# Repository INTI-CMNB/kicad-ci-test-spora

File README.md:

# KiCad CI/CD test using Spora

This project is a demo of [CI/CD](https://en.wikipedia.org/wiki/Continuous_integration) for [KiCad](https://www.kicad.org/)

## Objetive

Automate the following tasks:
* ERC and DRC checks
* PDF versions of the schematic and PCB for documentation
* Generation of fabrication files (BoMs, gerbers, drill, position, 3D model, etc.)

## Tools used

To automate the process here we use:
* [KiBot](https://github.com/INTI-CMNB/KiBot) to generate gerbers, drill, position files and BoMs (HTML, XLSX and CSV)
* [kicad-automation-scripts](https://github.com/INTI-CMNB/kicad-automation-scripts) to run DRC/ERC, print schematics and PCB
* [InteractiveHtmlBom](https://github.com/INTI-CMNB/InteractiveHtmlBom) to generate interactive HTML BoMs
* [PcbDraw](https://github.com/INTI-CMNB/PcbDraw) to generate the PCB previews using different colors
* Docker to integrate KiCad and all the tools in a single package suitable for CI/CD pipelines
* GitHub CI/CD pipeline mechanism

The docker image can be found [here](https://github.com/INTI-CMNB/kicad_auto)

## Test project

As a testbed we are using the [Spora](https://github.com/INTI-CMNB/spora) project. It contains three separated boards:
* **pcb_io** is the I/O module. 2 layers
* **pcb_main** is the main module. 6 layers.
* **pcb_prog** is the programmer interface. 2 layers.

## Here is what we test

The pipeline we test here runs 3 workflows, one for each PCB. Each workflow runs 4 jobs:

- ERC: Runs the Electrical Rules Check (schematic test).
- Schematic fabrication files: Generates all the outputs related to the schematic. Runs only if the ERC was successful.
- DRC: Runs the Design Rules Check (PCB test). Runs only if the ERC was successful.
- PCB fabrication files: Generates all the outputs related to the PCB. Runs only if the DRC was successful.

When a commit affects any of the schematics, PCBs or the associated Makefiles the workflow is started.

The configuration for the workflows can be found here: [.github/workflows/](https://github.com/INTI-CMNB/kicad-ci-test-spora/tree/master/.github/workflows)

To get the generated outputs you must enter in one of the workflows, [here is an example](https://github.com/INTI-CMNB/kicad-ci-test-spora/actions/runs/562325892).
Use the `Actions` option at the top of the page.

## Here is what we get

The summary of each workflow contains the generated files in a compressed ZIP. In the GitHub dialect these are the *artifacts*.
Here are links to the run #5 (2021-02-12):

- Main board:
  - [ERC report](https://github.com/INTI-CMNB/kicad-ci-test-spora/suites/2030327470/artifacts/40807405)
  - [DRC report](https://github.com/INTI-CMNB/kicad-ci-test-spora/suites/2030327470/artifacts/40807404)
  - [Schematic related stuff](https://github.com/INTI-CMNB/kicad-ci-test-spora/suites/2030327470/artifacts/40807407)
  - [PCB related stuff](https://github.com/INTI-CMNB/kicad-ci-test-spora/suites/2030327470/artifacts/40807406)
- I/O board:
  - [ERC report](https://github.com/INTI-CMNB/kicad-ci-test-spora/suites/2030327468/artifacts/40799887)
  - [DRC report](https://github.com/INTI-CMNB/kicad-ci-test-spora/suites/2030327468/artifacts/40799886)
  - [Schematic related stuff](https://github.com/INTI-CMNB/kicad-ci-test-spora/suites/2030327468/artifacts/40799889)
  - [PCB related stuff](https://github.com/INTI-CMNB/kicad-ci-test-spora/suites/2030327468/artifacts/40799888)
- Programmer board:
  - [ERC report](https://github.com/INTI-CMNB/kicad-ci-test-spora/suites/2030327465/artifacts/40799892)
  - [DRC report](https://github.com/INTI-CMNB/kicad-ci-test-spora/suites/2030327465/artifacts/40799891)
  - [Schematic related stuff](https://github.com/INTI-CMNB/kicad-ci-test-spora/suites/2030327465/artifacts/40799894)
  - [PCB related stuff](https://github.com/INTI-CMNB/kicad-ci-test-spora/suites/2030327465/artifacts/40799893)

## The KiBot configuration

The KiBot configuration files are:

- [Main board](https://github.com/INTI-CMNB/kicad-ci-test-spora/blob/master/pcb_main/spora.kibot.yaml)
- [I/O board](https://github.com/INTI-CMNB/kicad-ci-test-spora/blob/master/pcb_io/spora_io.kibot.yaml)
- [Programmer board](https://github.com/INTI-CMNB/kicad-ci-test-spora/blob/master/pcb_io/spora_io.kibot.yaml)

We also generate gerbers and drill files for some common manufacturers using the configurations found [here](https://github.com/INTI-CMNB/kicad-ci-test-spora/tree/master/configs)

## Original Spora README

BUILD AWESOME WEARABLES

Open hardware platform for wearables.

Lots of sensors ready to use, program and expand at ease. All packed in an incredible small size.
More info at [Spora web page](https://sporaio.com/).

Final release in [Spora repo](https://github.com/sporaio)

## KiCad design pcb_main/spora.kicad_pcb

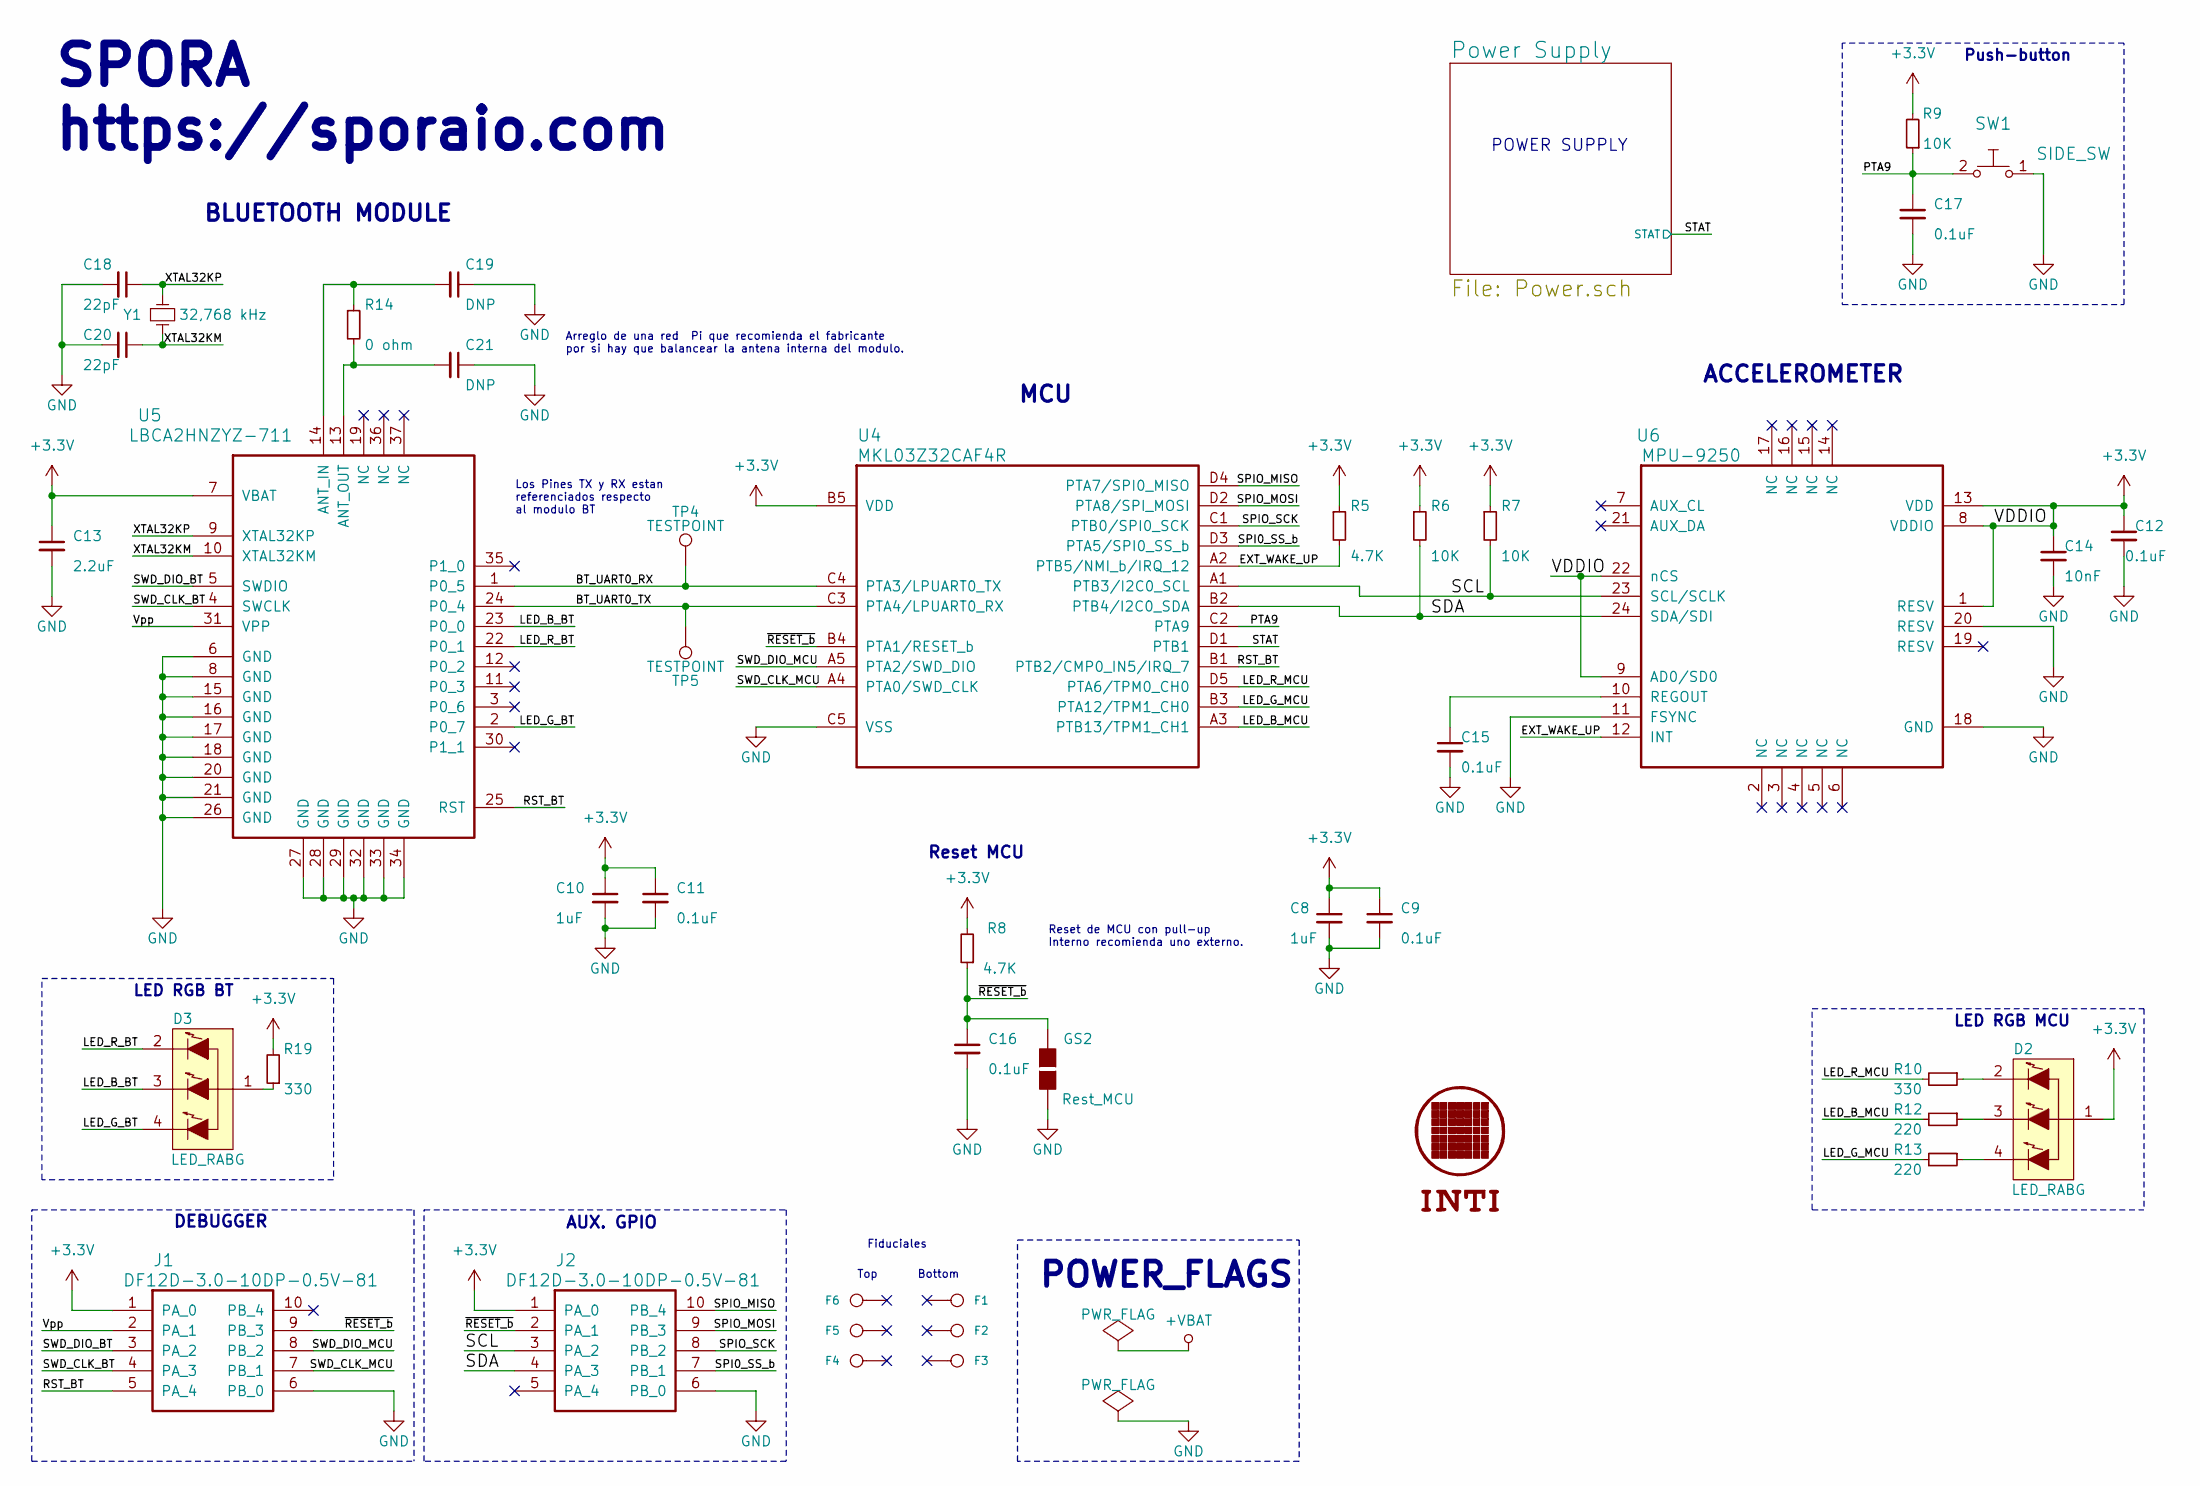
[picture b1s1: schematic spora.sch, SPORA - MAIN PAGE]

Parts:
C8, C10: 1uF; c_0201; digikey# 1276-6816-1-ND
C9, C11, C12, C15, C16, C17: 0.1uF; c_0201; digikey# 490-5405-1-ND
C13: 2.2uF; c_0201; digikey# 490-13224-1-ND
C14: 10nF; c_0201; digikey# 490-3166-1-ND
C18, C20: 22pF; c_0402; digikey# 732-7427-1-ND
C19, C21: DNP; c_0402
D2, D3: LED_RABG; SML-LX0404SIUPGUSB; digikey# 67-2125-1-ND
F1, F2, F3, F4, F5, F6: CONN_1; FIDUCIAL_65MIL
G1: LOGO_INTI
GS2: Rest_MCU; GS2
J1, J2: DF12D-3.0-10DP-0.5V-81; df12(3.0)-10dp-0.5v; digikey# H11736CT-ND
R5, R8: 4.7K; r_0201; digikey# 311-4.7KNCT-ND
R6, R7, R9: 10K; r_0201; digikey# 311-10KNCT-ND
R10, R19: 330; r_0201; digikey# 311-330NCT-ND
R12, R13: 220; r_0201; digikey# 311-220NCT-ND
R14: 0 ohm; r_0402; digikey# 311-0.0JRTR-ND
SW1: SIDE_SW; B3U_3000PB; digikey# SW1256DKR-ND
TP4, TP5: TESTPOINT
U4: MKL03Z32CAF4R; mouser# 841-MKL03Z32CAF4R; digikey# MKL03Z32CAF4RTR-ND
U5: LBCA2HNZYZ-711; LBCA2A2HNZYZ-711; digikey# 490-10561-1-ND
U6: MPU-9250; digikey# 1428-1019-1-ND
Y1: 32,768 kHz; ABS05-32.768KHZ-9-T; digikey# 535-11897-1-ND

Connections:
+3V3: C8.1, C9.1, C10.1, C11.1, C12.1, C13.1, C14.1, D2.1 (COMMON_ANODE), J1.1 (PA_0), J2.1 (PA_0), R5.1, R6.1, R7.1, R8.2, R9.2, R19.2, U4.B5 (VDD), U5.7 (VBAT), U6.1 (RESV), U6.8 (VDDIO), U6.9 (AD0/SD0), U6.13 (VDD), U6.22 (nCS); also elsewhere on the board
/BT_UART0_RX: TP4.1, U4.C4 (PTA3/LPUART0_TX), U5.1 (P0_5)
/BT_UART0_TX: TP5.1, U4.C3 (PTA4/LPUART0_RX), U5.24 (P0_4)
/EXT_WAKE_UP: R5.2, U4.A2 (PTB5/NMI_b/IRQ_12), U6.12 (INT)
/LED_B_BT: D3.3 (GREEN_CATHODE), U5.23 (P0_0)
/LED_B_MCU: R12.2, U4.A3 (PTB13/TPM1_CH1)
/LED_G_BT: D3.4 (BLUE_CATHODE), U5.2 (P0_7)
/LED_G_MCU: R13.2, U4.B3 (PTA12/TPM1_CH0)
/LED_R_BT: D3.2 (RED_CATHODE), U5.22 (P0_1)
/LED_R_MCU: R10.2, U4.D5 (PTA6/TPM0_CH0)
/PTA9: C17.1, R9.1, SW1.2, U4.C2 (PTA9)
/Power Supply/STAT: U4.D1 (PTB1); also elsewhere on the board
/RST_BT: J1.5 (PA_4), U4.B1 (PTB2/CMP0_IN5/IRQ_7), U5.25 (RST)
/SCL: J2.3 (PA_2), R7.2, U4.A1 (PTB3/I2C0_SCL), U6.23 (SCL/SCLK)
/SDA: J2.4 (PA_3), R6.2, U4.B2 (PTB4/I2C0_SDA), U6.24 (SDA/SDI)
/SPI0_SS_b: J2.7 (PB_1), U4.D3 (PTA5/SPI0_SS_b)
/SPIO_MISO: J2.10 (PB_4), U4.D4 (PTA7/SPI0_MISO)
/SPIO_MOSI: J2.9 (PB_3), U4.D2 (PTA8/SPI_MOSI)
/SPIO_SCK: J2.8 (PB_2), U4.C1 (PTB0/SPI0_SCK)
/SWD_CLK_BT: J1.4 (PA_3), U5.4 (SWCLK)
/SWD_CLK_MCU: J1.7 (PB_1), U4.A4 (PTA0/SWD_CLK)
/SWD_DIO_BT: J1.3 (PA_2), U5.5 (SWDIO)
/SWD_DIO_MCU: J1.8 (PB_2), U4.A5 (PTA2/SWD_DIO)
/Vpp: J1.2 (PA_1), U5.31 (VPP)
/XTAL32KM: C20.1, U5.10 (XTAL32KM), Y1.2
/XTAL32KP: C18.1, U5.9 (XTAL32KP), Y1.1
/~RESET_b: C16.1, GS2.1 (G1), J1.9 (PB_3), J2.2 (PA_1), R8.1, U4.B4 (PTA1/RESET_b)
GND: C8.2, C9.2, C10.2, C11.2, C12.2, C13.2, C14.2, C15.2, C16.2, C17.2, C18.2, C19.1, C20.2, C21.1, GS2.2 (G2), J1.6 (PB_0), J2.6 (PB_0), SW1.1, U4.C5 (VSS), U5.6 (GND), U5.8 (GND), U5.15 (GND), U5.16 (GND), U5.17 (GND), U5.18 (GND), U5.20 (GND), U5.21 (GND), U5.26 (GND), U5.27 (GND), U5.28 (GND), U5.29 (GND), U5.32 (GND), U5.33 (GND), U5.34 (GND), U6.11 (FSYNC), U6.18 (GND), U6.20 (RESV); also elsewhere on the board
unnamed: C15.1, U6.10 (REGOUT)
unnamed: C19.2, R14.1, U5.14 (ANT_IN)
unnamed: C21.2, R14.2, U5.13 (ANT_OUT)
unnamed: D2.2 (RED_CATHODE), R10.1
unnamed: D2.3 (GREEN_CATHODE), R12.1
unnamed: D2.4 (BLUE_CATHODE), R13.1
unnamed: D3.1 (COMMON_ANODE), R19.1

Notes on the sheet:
POWER_FLAGS
AUX. GPIO
Reset MCU
LED RGB MCU
Push-button
DEBUGGER
Los Pines TX y RX estan referenciados respecto al modulo BT
MCU
ACCELEROMETER
BLUETOOTH MODULE
Reset de MCU con pull-up Interno recomienda uno externo.
Arreglo de una red Pi que recomienda el fabricante por si hay que balancear la antena interna del modulo.
POWER SUPPLY
SPORA https://sporaio.com
LED RGB BT
Fiduciales
Top
Bottom

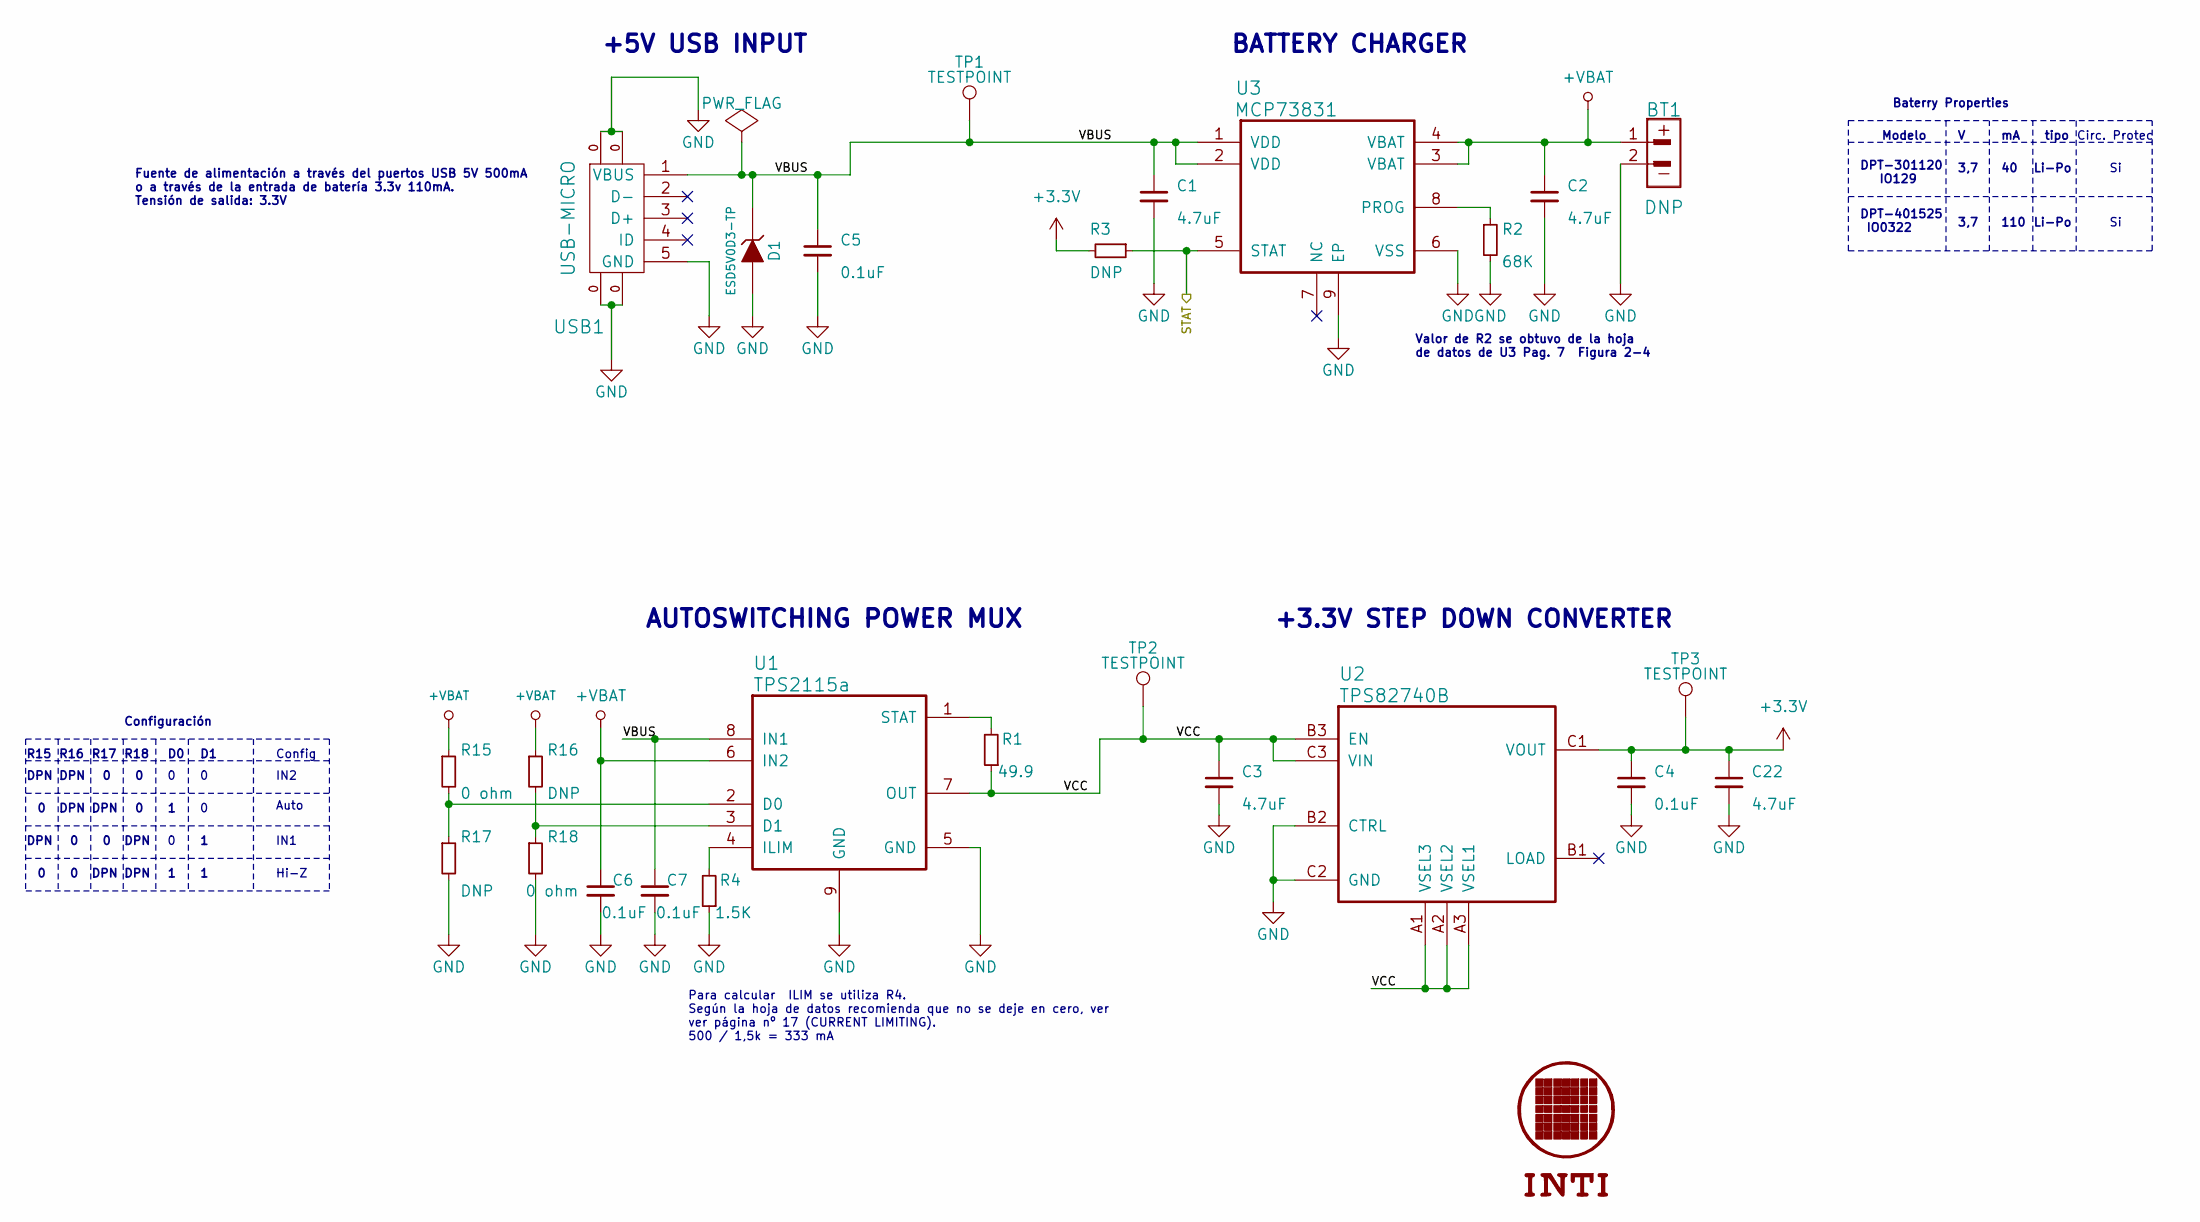
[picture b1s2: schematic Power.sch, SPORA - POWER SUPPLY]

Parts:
BT1: DNP; BAT_CON
C1, C2, C3, C22: 4.7uF; c_0201; digikey# 490-13230-1-ND
C4, C5, C6, C7: 0.1uF; c_0201; digikey# 490-5405-1-ND
D1: ESD5V0D3-TP; SOD-323; digikey# ESD5V0D3-TPMSCT-ND
G2: LOGO_INTI
R1: 49.9; r_0201; digikey# P49.9ABCT-ND
R2: 68K; r_0201; digikey# P68.0KABCT-ND
R3: DNP; r_0201; digikey# 311-470NCT-ND
R4: 1.5K; r_0201; digikey# 311-1.5KNCT-ND
R15, R18: 0 ohm; r_0402; digikey# 311-0.0JRCT-ND
R16, R17: DNP; r_0402
TP1, TP2, TP3: TESTPOINT
U1: TPS2115a; TPS2115A; digikey# 296-23394-1-ND
U2: TPS82740B; digikey# 296-37973-1-ND
U3: MCP73831; MCP73821; digikey# MCP73831-2ACI/MC-ND
USB1: USB-MICRO; conn_usb_B_micro_smd; digikey# H125279CT-ND

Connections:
+3V3: C4.1, C22.1, R3.2, TP3.1, U2.C1 (VOUT); also elsewhere on the board
+VBAT: BT1.1, C2.1, C6.1, R15.1, R16.1, U1.6 (IN2), U3.3 (VBAT), U3.4 (VBAT)
/Power Supply/STAT: R3.1, U3.5 (STAT); also elsewhere on the board
/Power Supply/VBUS: C1.1, C5.1, C7.1, D1.1 (K), TP1.1, U1.8 (IN1), U3.1 (VDD), U3.2 (VDD), USB1.1 (VBUS)
/Power Supply/VCC: C3.1, R1.1, TP2.1, U1.7 (OUT), U2.A1 (VSEL3), U2.A2 (VSEL2), U2.A3 (VSEL1), U2.B3 (EN), U2.C3 (VIN)
GND: BT1.2, C1.2, C2.2, C3.2, C4.2, C5.2, C6.2, C7.2, C22.2, D1.2 (A), R2.2, R4.1, R17.2, R18.2, U1.5 (GND), U1.9 (GND), U2.B2 (CTRL), U2.C2 (GND), U3.6 (VSS), U3.9 (EP), USB1.0, USB1.5 (GND); also elsewhere on the board
unnamed: R1.2, U1.1 (STAT)
unnamed: R2.1, U3.8 (PROG)
unnamed: R4.2, U1.4 (ILIM)
unnamed: R15.2, R17.1, U1.2 (D0)
unnamed: R16.2, R18.1, U1.3 (D1)

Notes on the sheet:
+3.3V STEP DOWN CONVERTER
AUTOSWITCHING POWER MUX
BATTERY CHARGER
+5V USB INPUT
Valor de R2 se obtuvo de la hoja de datos de U3 Pag. 7 Figura 2-4
Baterry Properties
Modelo
DPT-301120 IO129
DPT-401525 IO0322
3,7
110
tipo
Li-Po
Fuente de alimentación a través del puertos USB 5V 500mA o a través de la entrada de batería 3.3v 110mA. Tensión de salida: 3.3V
Para calcular ILIM se utiliza R4. Según la hoja de datos recomienda que no se deje en cero, ver ver página nº 17 (CURRENT LIMITING). 500 / 1,5k = 333 mA
Circ. Protec
Configuración
R15
R16
DPN
Config
R17
R18
Auto
IN2
IN1
Hi-Z

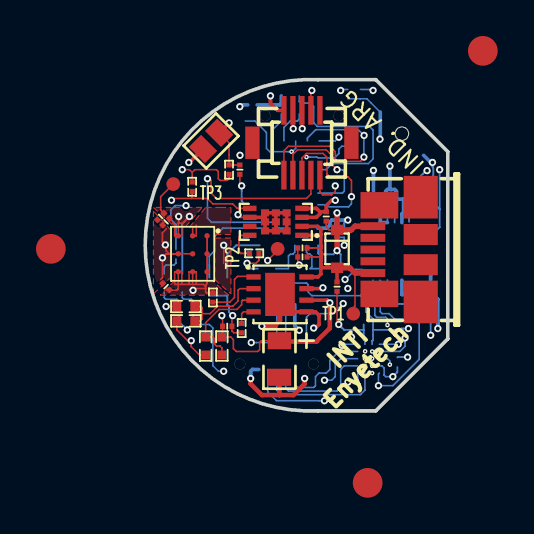
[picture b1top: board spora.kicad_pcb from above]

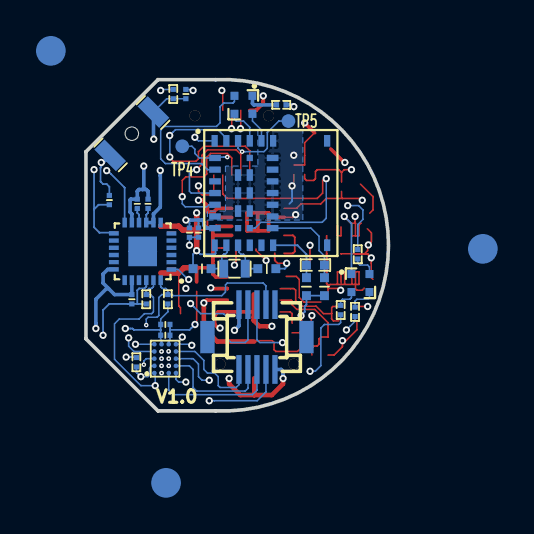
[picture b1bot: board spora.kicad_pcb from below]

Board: 6 copper layers, 16.8 x 18.4 mm, 67 parts (35 on the bottom side), 43 nets.

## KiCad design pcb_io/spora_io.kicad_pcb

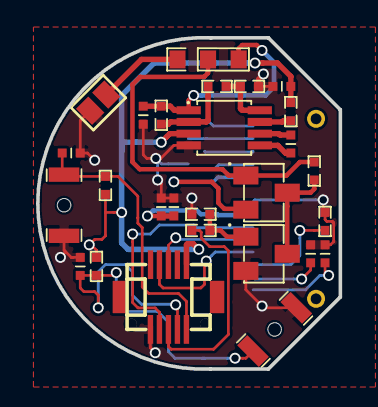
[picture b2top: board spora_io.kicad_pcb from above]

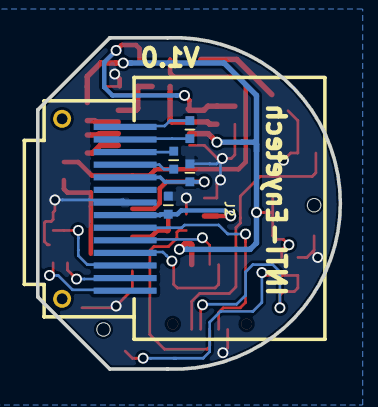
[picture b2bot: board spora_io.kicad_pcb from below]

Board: 2 copper layers, 16.8 x 18.4 mm, 32 parts (5 on the bottom side), 27 nets.

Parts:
C1, C2, C5, C6, C11, C12: 1uF; c_0402
C3: 2.2uF; c_0402
C4: 4.7uF; c_0402
C7, C8: 0.1uF; c_0402
C9, C10: 10 uF; c_0402
C13: 1 uF; c_0402
CON2: VBA_IN; GS2
J1: DF12B 3.0 10DS 0.5V 81; df12(3.0)-10ds-0.5v
J2: ER-OLED0.49-1Series; ER-OLED0.49-1_B
JP1: JUMPER; JUMPER3_0603
Q1: FDN335N_NMOS; SSOT-3
Q2: FDN338P_PMOS; SSOT-3
R1: 390K; r_0402
R2, R3, R7, R9, R10, R11: 10K; r_0402
R6: 23.2 K; r_0402
R12: 0 ohm; r_0402
R13: 100K; r_0402
SW1, SW2: SW_PUSH; B3U_3000PB
U1: MCP1252-ADJ; MSOP-8

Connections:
+3V3: C9.1, J1.1, R2.1, R3.1, R13.1, U1.3
/BOTON_CENTRO: C8.1, J1.10, R3.2, SW2.2
/BOTON_IZQUIERDO: C7.1, J1.9, R2.2, SW1.2
/GPIO_OLED: J1.8, R12.1
/RESET_OLED: J1.7, J2.9
/SCL: J1.3, J2.10
/SDA: J1.4, J2.11
/VBAT: C5.1, J2.5, Q2.2
/VBAT_+: CON2.1, JP1.3
/VBAT_DC_DC: C10.1, JP1.1, R11.1, U1.1
/VBAT_IN: JP1.2, Q2.1, R10.1
/VDD: C6.1, C11.1, C12.1, J2.8
GND: C3.2, C4.2, C5.2, C6.2, C7.2, C8.2, C9.2, C10.2, C11.2, C12.2, CON2.2, J1.6, J2.7, Q1.2, R1.2, R7.2, R9.2, SW1.1, SW2.1, U1.4
unnamed: C1.1, J2.2
unnamed: C1.2, J2.1
unnamed: C2.1, J2.3
unnamed: C2.2, J2.4
unnamed: C3.1, J2.14
unnamed: C4.1, J2.13
unnamed: C13.1, U1.6
unnamed: C13.2, U1.5
unnamed: J2.12, R1.1
unnamed: Q1.1, R9.1, R12.2
unnamed: Q1.3, Q2.3, R10.2
unnamed: R6.2, R7.1, U1.8
unnamed: R6.1, R11.2, U1.2
unnamed: R13.2, U1.7

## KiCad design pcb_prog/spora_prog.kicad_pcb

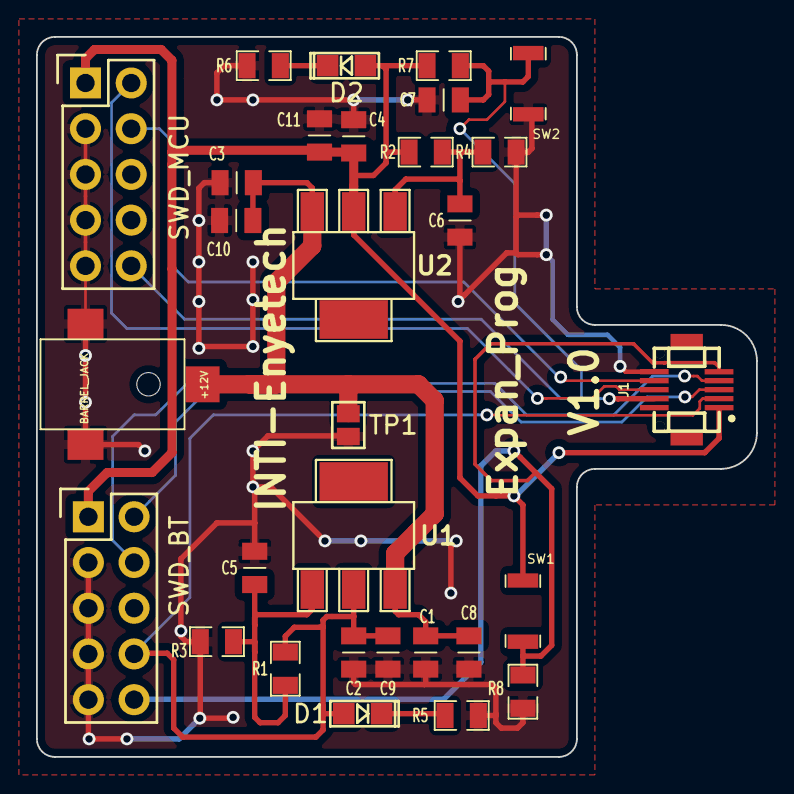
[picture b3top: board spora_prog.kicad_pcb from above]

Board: 2 copper layers, 40.0 x 40.0 mm, 30 parts (0 on the bottom side), 14 nets.

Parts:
+12V: BARREL_JACK; Pj-38-smt
C1, C2, C3, C4, C5, C6: 10uF; c_0805
C7, C8, C9, C10, C11: 0.1uF; c_0805
D1, D2: Led; LED-0805
J1: DF12B-3.0-10DS-0.5V-81; df12(3.0)-10ds-0.5v
R1: 270; r_0805
R2: 470; r_0805
R3: 1,2k; r_0805
R4: 280; r_0805
R5: 10K; r_0805
R6, R7: 4,7K; r_0805
R8: 4K7; r_0805
SW1, SW2: SIDE_SW; B3U_1000PB
SWD_BT: SWD_BT; Pin_Header_Straight_2x05
SWD_MCU: SWD_MCU; Pin_Header_Straight_2x05
TP1: TP1; GS2
U1, U2: LM1117; sot223

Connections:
+3V3: C4.1, C11.1, D2.2, J1.1, R2.1, R7.2, SW1.2, SWD_BT.1, SWD_MCU.1, U2.2
+12V: +12V.1, C1.1, C3.1, C8.1, C10.1, TP1.1, U1.3, U2.3
/RST_BT: J1.5, R8.2, SW1.1, SWD_BT.10
/SWD_CLK_BT: J1.4, SWD_BT.4
/SWD_CLK_MCU: J1.7, SWD_MCU.4
/SWD_DIO_BT: J1.3, SWD_BT.2
/SWD_DIO_MCU: J1.8, SWD_MCU.2
/~RESET_b: C7.1, J1.9, R7.1, SW2.2, SWD_MCU.10
GND: +12V.2, +12V.3, C1.2, C2.2, C3.2, C4.2, C5.2, C6.2, C7.2, C8.2, C9.2, C10.2, C11.2, J1.6, R3.2, R4.2, R5.1, R6.1, R8.1, SW2.1, SWD_BT.3, SWD_BT.5, SWD_BT.7, SWD_BT.9, SWD_MCU.3, SWD_MCU.5, SWD_MCU.7, SWD_MCU.9, TP1.2
unnamed: C5.1, R1.2, R3.1, U1.1
unnamed: C6.1, R2.2, R4.1, U2.1
unnamed: D1.1, R5.2
unnamed: D2.1, R6.2
VPP: C2.1, C9.1, D1.2, J1.2, R1.1, SWD_BT.8, U1.2

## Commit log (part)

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2020-08-25 Added CI/CD pipeline files.
2020-08-25 Added project information.
2020-08-25 Added the project files.
2020-08-25 Excluded the */Fabrication/ dirs from git.
2020-08-25 Removed `check_zone_fills` obsolete option.
2020-08-25 Unified the file name outputs for the pcb_main.
    Is an example of how to achieve uniform output names.
2020-08-25 Added SETEdit project to the list of excluded files.
2020-08-26 Fixed output directories for each sub-project.
2020-08-26 Added the pipeline YAMLs as triggers.
2020-08-26 Updated the README.md
2020-08-26 Added links to workflows in the badgets
2020-08-26 Added example of output files.
2021-02-12 Added KiBot configuration files for 5 manufacturers
2021-02-12 Added 3D STEP models for most of pcb_main.
2021-02-12 Adapted pcb_main to use the STEP models.
2021-02-12 Adapted configs and makefiles to newer features.
    - Makefiles rely on generated makefiles.
    - Adapted obsolete exclude_any option (now using filters)
    - Added Elecrow, FusionPCB, JLCPCB, P-Ban and PCBWay gerbers generation
2021-02-12 Adapted worflows to always get the results and include the log
2021-02-12 Switching to upload-artifact v2
2021-02-12 Added more information to the readme
2021-05-04 Added test using the GitHub Action
2021-05-04 Fixed the path to the images.
    - This test runs KiBot from the root of the project.
2021-05-04 Renamed the artifacts to be more descriptive.
2021-08-24 Fixed PCBWay drill format. Closes #1
2021-11-10 Update README.md
    https://forum.kicad.info/t/warning-avoid-all-links-to-kicad-pcb-org-use-kicad-org/31521
2023-01-27 Updated the workflows
2023-01-27 Updated workflows
2024-08-27 Actions forced

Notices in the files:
pcb_main/Power.sch:
BSD License.  See LICENSE.txt file
